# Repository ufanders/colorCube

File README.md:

# colorCube
Here lies schematic, PCB layout and firmware for a very tiny 4x4x4 RGB LED cube.

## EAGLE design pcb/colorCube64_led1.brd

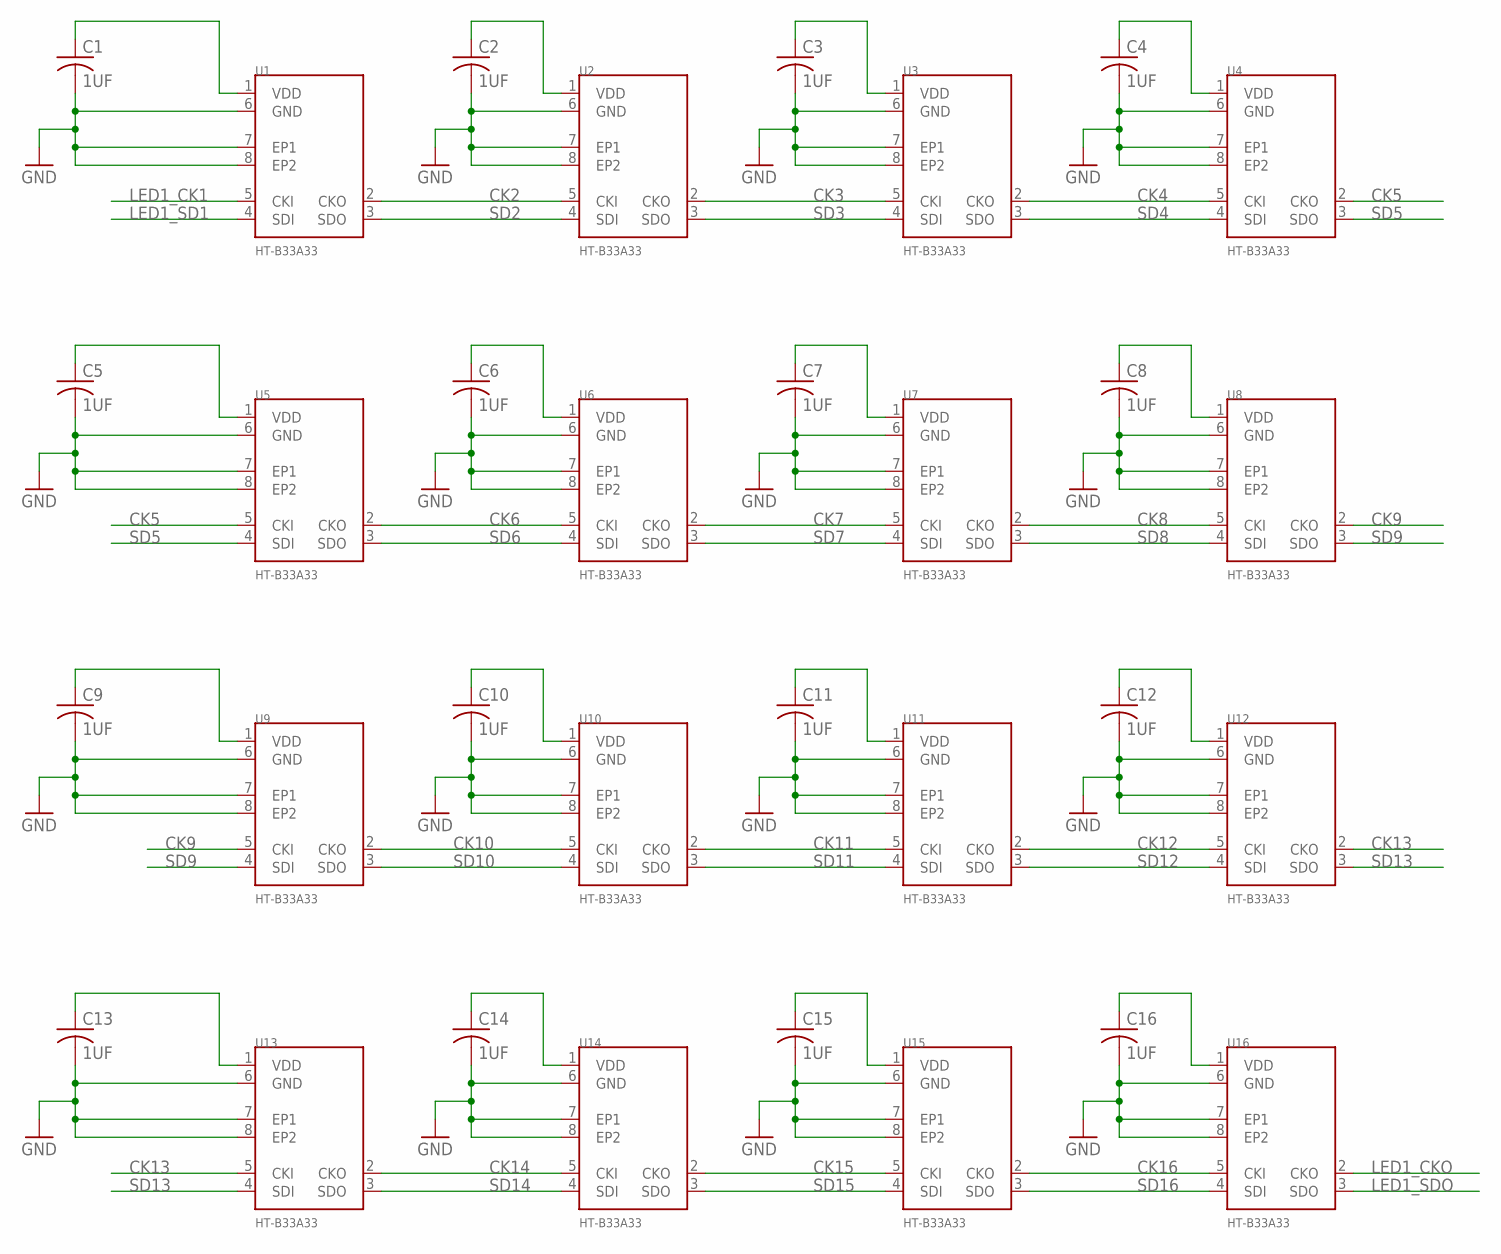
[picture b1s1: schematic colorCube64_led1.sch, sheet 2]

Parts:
C1, C2, C3, C4, C5, C6, C7, C8, C9, C10, C11, C12, C13, C14, C15, C16: 1UF; C0201
U1, U2, U3, U4, U5, U6, U7, U8, U9, U10, U11, U12, U13, U14, U15, U16: HT-B33A33; HT-B33A3

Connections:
CK2: U1.2 (CKO), U2.5 (CKI)
CK3: U2.2 (CKO), U3.5 (CKI)
CK4: U3.2 (CKO), U4.5 (CKI)
CK5: U4.2 (CKO), U5.5 (CKI)
CK6: U5.2 (CKO), U6.5 (CKI)
CK7: U6.2 (CKO), U7.5 (CKI)
CK8: U7.2 (CKO), U8.5 (CKI)
CK9: U8.2 (CKO), U9.5 (CKI)
CK10: U9.2 (CKO), U10.5 (CKI)
CK11: U10.2 (CKO), U11.5 (CKI)
CK12: U11.2 (CKO), U12.5 (CKI)
CK13: U12.2 (CKO), U13.5 (CKI)
CK14: U13.2 (CKO), U14.5 (CKI)
CK15: U14.2 (CKO), U15.5 (CKI)
CK16: U15.2 (CKO), U16.5 (CKI)
GND: C1.2, C2.2, C3.2, C4.2, C5.2, C6.2, C7.2, C8.2, C9.2, C10.2, C11.2, C12.2, C13.2, C14.2, C15.2, C16.2, U1.6 (GND), U1.7 (EP1), U1.8 (EP2), U2.6 (GND), U2.7 (EP1), U2.8 (EP2), U3.6 (GND), U3.7 (EP1), U3.8 (EP2), U4.6 (GND), U4.7 (EP1), U4.8 (EP2), U5.6 (GND), U5.7 (EP1), U5.8 (EP2), U6.6 (GND), U6.7 (EP1), U6.8 (EP2), U7.6 (GND), U7.7 (EP1), U7.8 (EP2), U8.6 (GND), U8.7 (EP1), U8.8 (EP2), U9.6 (GND), U9.7 (EP1), U9.8 (EP2), U10.6 (GND), U10.7 (EP1), U10.8 (EP2), U11.6 (GND), U11.7 (EP1), U11.8 (EP2), U12.6 (GND), U12.7 (EP1), U12.8 (EP2), U13.6 (GND), U13.7 (EP1), U13.8 (EP2), U14.6 (GND), U14.7 (EP1), U14.8 (EP2), U15.6 (GND), U15.7 (EP1), U15.8 (EP2), U16.6 (GND), U16.7 (EP1), U16.8 (EP2)
LED1_CK1: U1.5 (CKI)
LED1_CKO: U16.2 (CKO)
LED1_SD1: U1.4 (SDI)
LED1_SDO: U16.3 (SDO)
unnamed: C2.1, U2.1 (VDD)
unnamed: C3.1, U3.1 (VDD)
unnamed: C4.1, U4.1 (VDD)
unnamed: C5.1, U5.1 (VDD)
unnamed: C6.1, U6.1 (VDD)
unnamed: C7.1, U7.1 (VDD)
unnamed: C8.1, U8.1 (VDD)
unnamed: C9.1, U9.1 (VDD)
unnamed: C10.1, U10.1 (VDD)
unnamed: C11.1, U11.1 (VDD)
unnamed: C12.1, U12.1 (VDD)
unnamed: C13.1, U13.1 (VDD)
unnamed: C14.1, U14.1 (VDD)
unnamed: C15.1, U15.1 (VDD)
unnamed: C16.1, U16.1 (VDD)
unnamed: C1.1, U1.1 (VDD)
SD2: U1.3 (SDO), U2.4 (SDI)
SD3: U2.3 (SDO), U3.4 (SDI)
SD4: U3.3 (SDO), U4.4 (SDI)
SD5: U4.3 (SDO), U5.4 (SDI)
SD6: U5.3 (SDO), U6.4 (SDI)
SD7: U6.3 (SDO), U7.4 (SDI)
SD8: U7.3 (SDO), U8.4 (SDI)
SD9: U8.3 (SDO), U9.4 (SDI)
SD10: U9.3 (SDO), U10.4 (SDI)
SD11: U10.3 (SDO), U11.4 (SDI)
SD12: U11.3 (SDO), U12.4 (SDI)
SD13: U12.3 (SDO), U13.4 (SDI)
SD14: U13.3 (SDO), U14.4 (SDI)
SD15: U14.3 (SDO), U15.4 (SDI)
SD16: U15.3 (SDO), U16.4 (SDI)

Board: 2 copper layers, 32 parts (0 on the bottom side), 47 nets, no tracks yet.

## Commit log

2017-01-26 -Created LED part. -Started FPC 1 of 4.
